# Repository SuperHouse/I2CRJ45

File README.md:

I2C to RJ45 Breakouts for Light Switch Controller
=================================================

Copyright 2019-2021 SuperHouse Automation Pty Ltd  www.superhouse.tv

These I2C to RJ45 breakouts are one component of the SuperHouse home
automation light switch controller project. They allow light switches
to be connected to a controller such as an Arduino, Raspberry Pi,
or ESP8266/ESP32 board.

The RJ45 sockets on the breakout are connected to I/O channels via
I2C addressable I/O buffers. Each RJ45 socket provides connections for
GND, 12V, and 4 signal lines.

Features:

 * RJ45 sockets for connection to light switches over Cat-5
 * I2C interface with interrupt output

More information on the Light Switch Controller project:

  http://www.superhouse.tv/lsc

The LSC also has its own GitHub repo which includes example firmware:

  https://github.com/SuperHouse/LSC

Purchase these breakouts pre-assembled:

  http://www.superhouse.tv/i2crj45

INSTALLATION
------------
The design is saved as an EAGLE project. EAGLE PCB design software is
available from www.cadsoftusa.com free for non-commercial use. To use
this project download it and place the directory containing these files
into the "eagle" directory on your computer. Then open EAGLE and
navigate to the project.

CREDITS
-------
Designed by Jonathan Oxer jon@oxer.com.au

Mechanical drawings by Aaron Knox

DISTRIBUTION
------------
The specific terms of distribution of this project are governed by the
license referenced below.

LICENSE
-------
Licensed under the TAPR Open Hardware License (www.tapr.org/OHL).
The "license" folder within this repository also contains a copy of
this license in plain text format.

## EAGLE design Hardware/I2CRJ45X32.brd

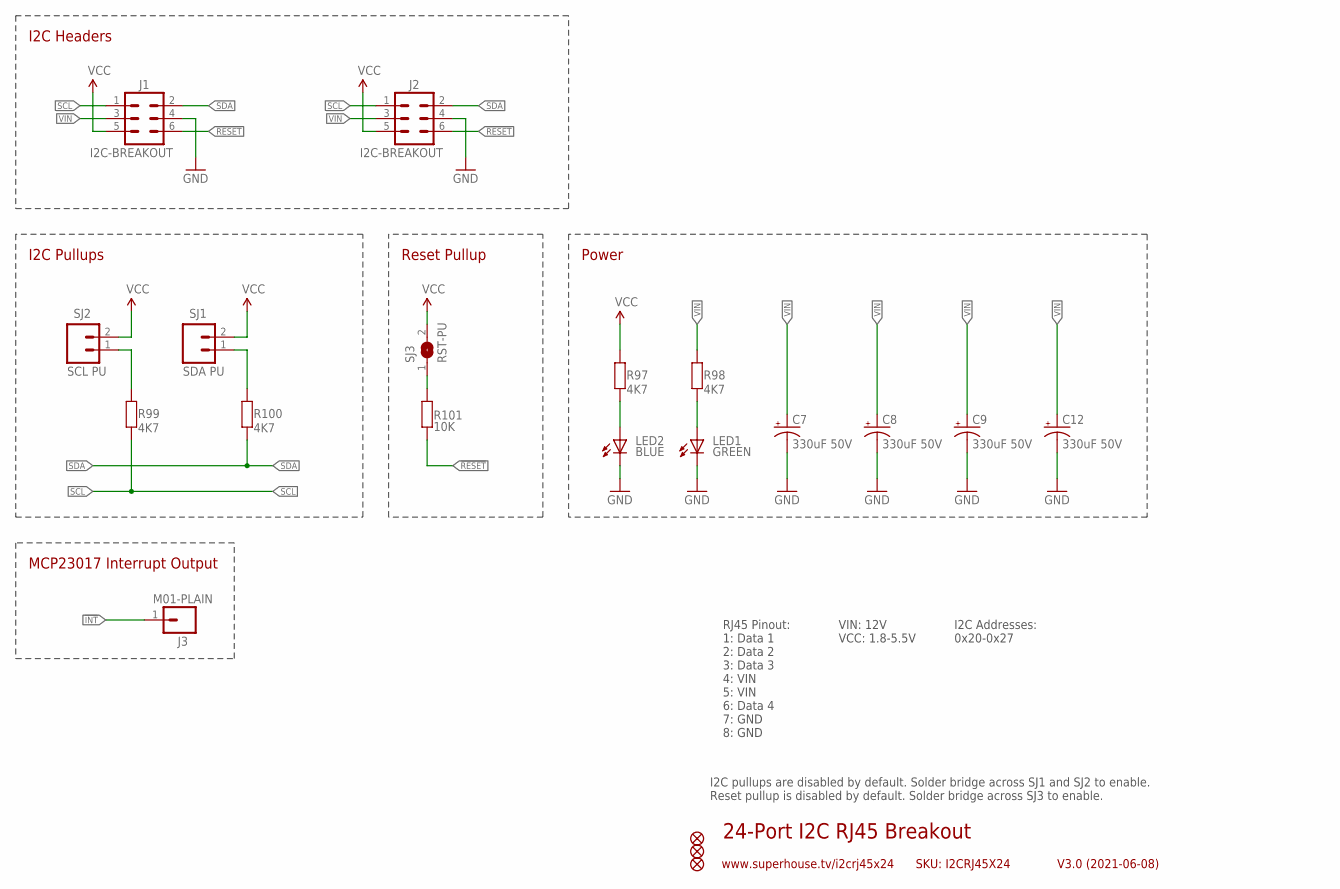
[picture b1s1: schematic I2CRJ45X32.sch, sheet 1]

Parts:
C7, C8, C9, C12: 330uF 50V; PANASONIC_G
FID1, FID2, FID3: FIDUCIAL1X2.5; FIDUCIAL-1X2.5
J1, J2: I2C-BREAKOUT; 2X3-2.54-SHROUDED
J3: M01-PLAIN; 1X01
LED1: GREEN; LED-0603
LED2: BLUE; LED-0603
R97, R98, R99, R100: 4K7; R0603
R101: 10K; R0603
SJ1: SDA PU; 1X02-P
SJ2: SCL PU; 1X02-P
SJ3: RST-PU; SJ

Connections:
!INT: J3.1; also elsewhere on the board
!RESET: J1.6, J2.6, R101.1; also elsewhere on the board
GND: C7.-, C8.-, C9.-, C12.-, J1.4, J2.4, LED1.C, LED2.C; also elsewhere on the board
unnamed: R99.2, SJ2.1
unnamed: R100.2, SJ1.1
unnamed: R101.2, SJ3.1
unnamed: LED2.A, R97.1
unnamed: LED1.A, R98.1
SCL: J1.1, J2.1, R99.1; also elsewhere on the board
SDA: J1.2, J2.2, R100.1; also elsewhere on the board
VCC: J1.5, J2.5, R97.2, SJ1.2, SJ2.2, SJ3.2; also elsewhere on the board
VIN: C7.+, C8.+, C9.+, C12.+, J1.3, J2.3, R98.2; also elsewhere on the board

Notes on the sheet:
24-Port I2C RJ45 Breakout
V3.0 (2021-06-08)
www.superhouse.tv/i2crj45x24
SKU: I2CRJ45X24
RJ45 Pinout: 1: Data 1 2: Data 2 3: Data 3 4: VIN 5: VIN 6: Data 4 7: GND 8: GND
VIN: 12V VCC: 1.8-5.5V
I2C Addresses: 0x20-0x27
I2C Headers
MCP23017 Interrupt Output
I2C Pullups
I2C pullups are disabled by default. Solder bridge across SJ1 and SJ2 to enable. Reset pullup is disabled by default. Solder bridge across SJ3 to enable.
Power
Reset Pullup

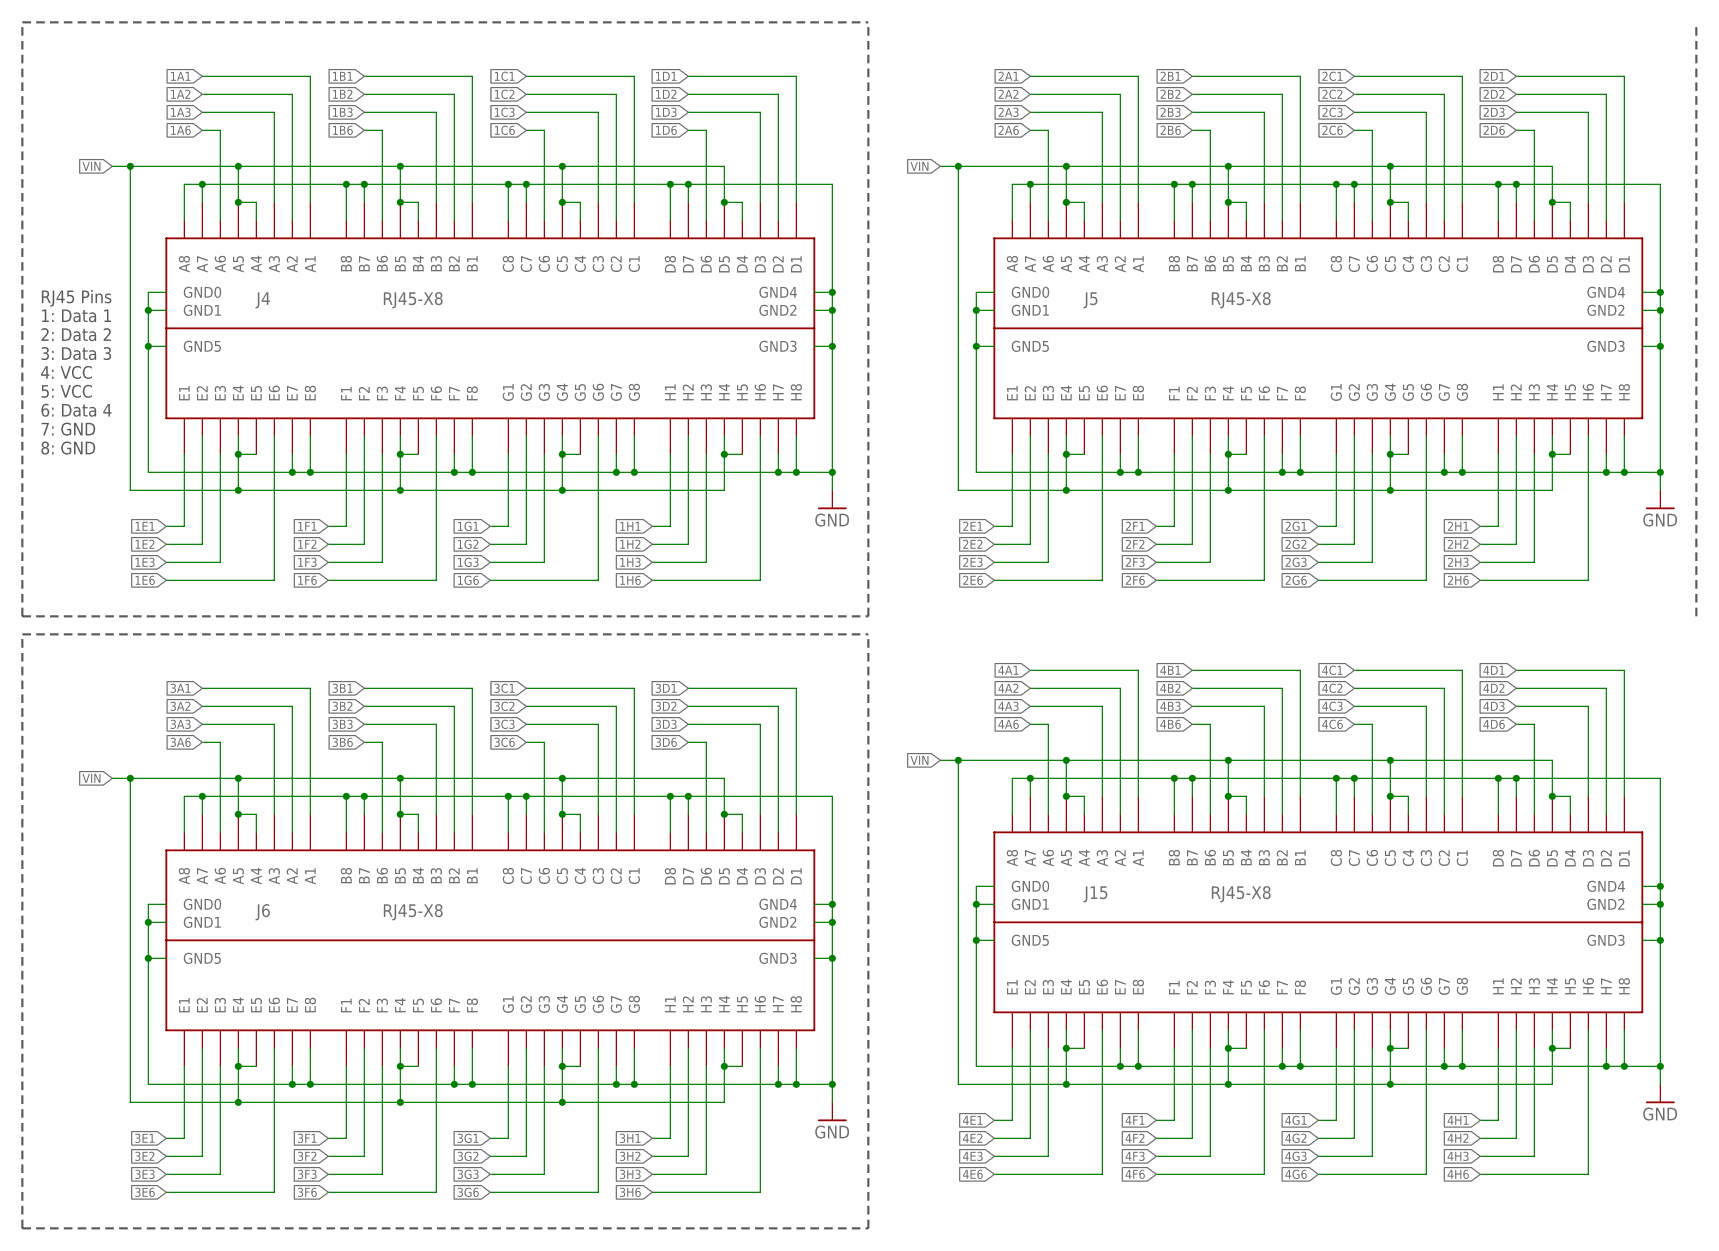
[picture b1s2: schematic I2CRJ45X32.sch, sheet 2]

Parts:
J4, J5, J6, J15: RJ45-X8; RJ45-2X4

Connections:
1A1: J4.A1; also elsewhere on the board
1A2: J4.A2; also elsewhere on the board
1A3: J4.A3; also elsewhere on the board
1A6: J4.A6; also elsewhere on the board
1B1: J4.B1; also elsewhere on the board
1B2: J4.B2; also elsewhere on the board
1B3: J4.B3; also elsewhere on the board
1B6: J4.B6; also elsewhere on the board
1C1: J4.C1; also elsewhere on the board
1C2: J4.C2; also elsewhere on the board
1C3: J4.C3; also elsewhere on the board
1C6: J4.C6; also elsewhere on the board
1D1: J4.D1; also elsewhere on the board
1D2: J4.D2; also elsewhere on the board
1D3: J4.D3; also elsewhere on the board
1D6: J4.D6; also elsewhere on the board
1E1: J4.E1; also elsewhere on the board
1E2: J4.E2; also elsewhere on the board
1E3: J4.E3; also elsewhere on the board
1E6: J4.E6; also elsewhere on the board
1F1: J4.F1; also elsewhere on the board
1F2: J4.F2; also elsewhere on the board
1F3: J4.F3; also elsewhere on the board
1F6: J4.F6; also elsewhere on the board
1G1: J4.G1; also elsewhere on the board
1G2: J4.G2; also elsewhere on the board
1G3: J4.G3; also elsewhere on the board
1G6: J4.G6; also elsewhere on the board
1H1: J4.H1; also elsewhere on the board
1H2: J4.H2; also elsewhere on the board
1H3: J4.H3; also elsewhere on the board
1H6: J4.H6; also elsewhere on the board
2A1: J5.A1; also elsewhere on the board
2A2: J5.A2; also elsewhere on the board
2A3: J5.A3; also elsewhere on the board
2A6: J5.A6; also elsewhere on the board
2B1: J5.B1; also elsewhere on the board
2B2: J5.B2; also elsewhere on the board
2B3: J5.B3; also elsewhere on the board
2B6: J5.B6; also elsewhere on the board
2C1: J5.C1; also elsewhere on the board
2C2: J5.C2; also elsewhere on the board
2C3: J5.C3; also elsewhere on the board
2C6: J5.C6; also elsewhere on the board
2D1: J5.D1; also elsewhere on the board
2D2: J5.D2; also elsewhere on the board
2D3: J5.D3; also elsewhere on the board
2D6: J5.D6; also elsewhere on the board
2E1: J5.E1; also elsewhere on the board
2E2: J5.E2; also elsewhere on the board
2E3: J5.E3; also elsewhere on the board
2E6: J5.E6; also elsewhere on the board
2F1: J5.F1; also elsewhere on the board
2F2: J5.F2; also elsewhere on the board
2F3: J5.F3; also elsewhere on the board
2F6: J5.F6; also elsewhere on the board
2G1: J5.G1; also elsewhere on the board
2G2: J5.G2; also elsewhere on the board
2G3: J5.G3; also elsewhere on the board
2G6: J5.G6; also elsewhere on the board
2H1: J5.H1; also elsewhere on the board
2H2: J5.H2; also elsewhere on the board
2H3: J5.H3; also elsewhere on the board
2H6: J5.H6; also elsewhere on the board
3A1: J6.A1; also elsewhere on the board
3A2: J6.A2; also elsewhere on the board
3A3: J6.A3; also elsewhere on the board
3A6: J6.A6; also elsewhere on the board
3B1: J6.B1; also elsewhere on the board
3B2: J6.B2; also elsewhere on the board
3B3: J6.B3; also elsewhere on the board
3B6: J6.B6; also elsewhere on the board
3C1: J6.C1; also elsewhere on the board
3C2: J6.C2; also elsewhere on the board
3C3: J6.C3; also elsewhere on the board
3C6: J6.C6; also elsewhere on the board
3D1: J6.D1; also elsewhere on the board
3D2: J6.D2; also elsewhere on the board
3D3: J6.D3; also elsewhere on the board
3D6: J6.D6; also elsewhere on the board
3E1: J6.E1; also elsewhere on the board
3E2: J6.E2; also elsewhere on the board
3E3: J6.E3; also elsewhere on the board
3E6: J6.E6; also elsewhere on the board
3F1: J6.F1; also elsewhere on the board
3F2: J6.F2; also elsewhere on the board
3F3: J6.F3; also elsewhere on the board
3F6: J6.F6; also elsewhere on the board
3G1: J6.G1; also elsewhere on the board
3G2: J6.G2; also elsewhere on the board
3G3: J6.G3; also elsewhere on the board
3G6: J6.G6; also elsewhere on the board
3H1: J6.H1; also elsewhere on the board
3H2: J6.H2; also elsewhere on the board
3H3: J6.H3; also elsewhere on the board
3H6: J6.H6; also elsewhere on the board
4A1: J15.A1; also elsewhere on the board
4A2: J15.A2; also elsewhere on the board
4A3: J15.A3; also elsewhere on the board
4A6: J15.A6; also elsewhere on the board
4B1: J15.B1; also elsewhere on the board
4B2: J15.B2; also elsewhere on the board
4B3: J15.B3; also elsewhere on the board
4B6: J15.B6; also elsewhere on the board
4C1: J15.C1; also elsewhere on the board
4C2: J15.C2; also elsewhere on the board
4C3: J15.C3; also elsewhere on the board
4C6: J15.C6; also elsewhere on the board
4D1: J15.D1; also elsewhere on the board
4D2: J15.D2; also elsewhere on the board
4D3: J15.D3; also elsewhere on the board
4D6: J15.D6; also elsewhere on the board
4E1: J15.E1; also elsewhere on the board
4E2: J15.E2; also elsewhere on the board
4E3: J15.E3; also elsewhere on the board
4E6: J15.E6; also elsewhere on the board
4F1: J15.F1; also elsewhere on the board
4F2: J15.F2; also elsewhere on the board
4F3: J15.F3; also elsewhere on the board
4F6: J15.F6; also elsewhere on the board
4G1: J15.G1; also elsewhere on the board
4G2: J15.G2; also elsewhere on the board
4G3: J15.G3; also elsewhere on the board
4G6: J15.G6; also elsewhere on the board
4H1: J15.H1; also elsewhere on the board
4H2: J15.H2; also elsewhere on the board
4H3: J15.H3; also elsewhere on the board
4H6: J15.H6; also elsewhere on the board
GND: J4.A7, J4.A8, J4.B7, J4.B8, J4.C7, J4.C8, J4.D7, J4.D8, J4.E7, J4.E8, J4.F7, J4.F8, J4.G7, J4.G8, J4.GND0, J4.GND1, J4.GND2, J4.GND3, J4.GND4, J4.GND5, J4.H7, J4.H8, J5.A7, J5.A8, J5.B7, J5.B8, J5.C7, J5.C8, J5.D7, J5.D8, J5.E7, J5.E8, J5.F7, J5.F8, J5.G7, J5.G8, J5.GND0, J5.GND1, J5.GND2, J5.GND3, J5.GND4, J5.GND5, J5.H7, J5.H8, J6.A7, J6.A8, J6.B7, J6.B8, J6.C7, J6.C8, J6.D7, J6.D8, J6.E7, J6.E8, J6.F7, J6.F8, J6.G7, J6.G8, J6.GND0, J6.GND1, J6.GND2, J6.GND3, J6.GND4, J6.GND5, J6.H7, J6.H8, J15.A7, J15.A8, J15.B7, J15.B8, J15.C7, J15.C8, J15.D7, J15.D8, J15.E7, J15.E8, J15.F7, J15.F8, J15.G7, J15.G8, J15.GND0, J15.GND1, J15.GND2, J15.GND3, J15.GND4, J15.GND5, J15.H7, J15.H8; also elsewhere on the board
VIN: J4.A4, J4.A5, J4.B4, J4.B5, J4.C4, J4.C5, J4.D4, J4.D5, J4.E4, J4.E5, J4.F4, J4.F5, J4.G4, J4.G5, J4.H4, J4.H5, J5.A4, J5.A5, J5.B4, J5.B5, J5.C4, J5.C5, J5.D4, J5.D5, J5.E4, J5.E5, J5.F4, J5.F5, J5.G4, J5.G5, J5.H4, J5.H5, J6.A4, J6.A5, J6.B4, J6.B5, J6.C4, J6.C5, J6.D4, J6.D5, J6.E4, J6.E5, J6.F4, J6.F5, J6.G4, J6.G5, J6.H4, J6.H5, J15.A4, J15.A5, J15.B4, J15.B5, J15.C4, J15.C5, J15.D4, J15.D5, J15.E4, J15.E5, J15.F4, J15.F5, J15.G4, J15.G5, J15.H4, J15.H5; also elsewhere on the board

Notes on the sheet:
RJ45 Pins 1: Data 1 2: Data 2 3: Data 3 4: VCC 5: VCC 6: Data 4 7: GND 8: GND

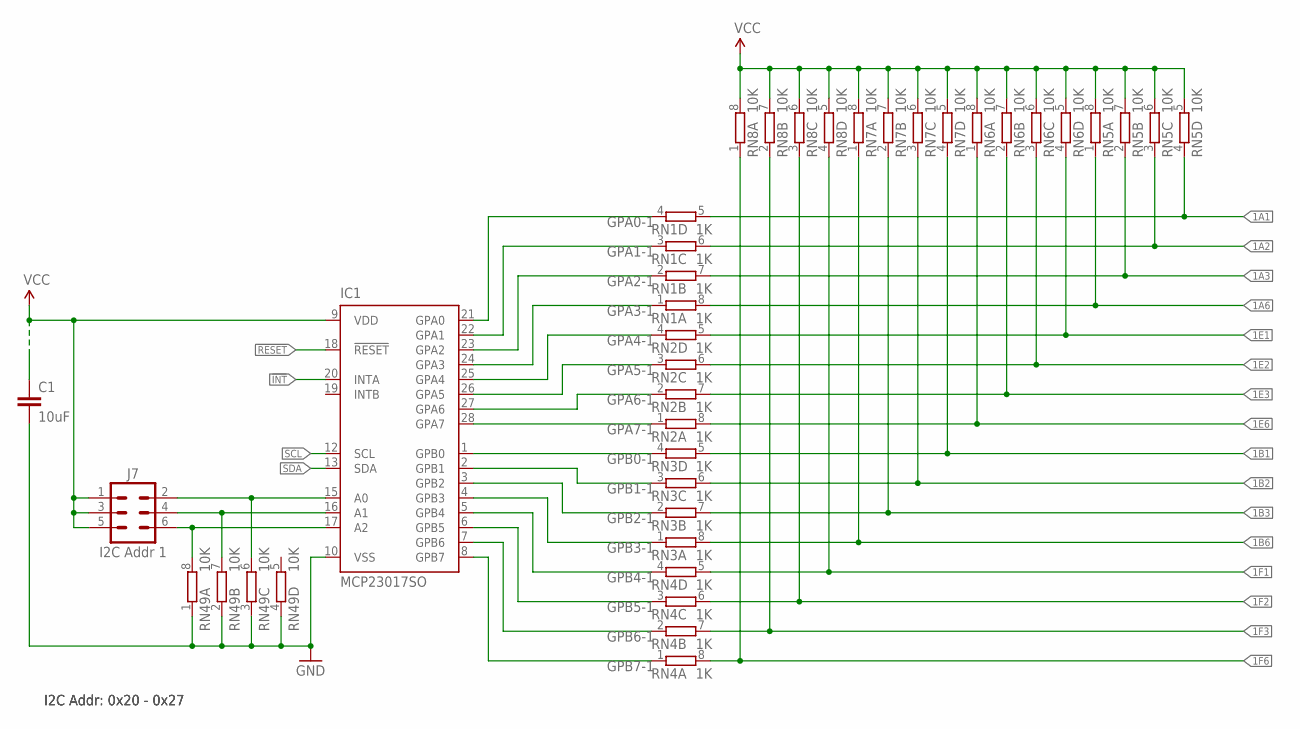
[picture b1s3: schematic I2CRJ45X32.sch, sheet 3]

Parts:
C1: 10uF; C0805
IC1: MCP23017SO; SO28W
J7: I2C Addr 1; 2X03-P
RN1, RN2, RN3, RN4: 1K; CAY16
RN5, RN6, RN7, RN8, RN49: 10K; CAY16

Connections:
1A1: RN1.5 (2), RN5.4 (1); also elsewhere on the board
1A2: RN1.6 (2), RN5.3 (1); also elsewhere on the board
1A3: RN1.7 (2), RN5.2 (1); also elsewhere on the board
1A6: RN1.8 (2), RN5.1; also elsewhere on the board
1B1: RN3.5 (2), RN7.4 (1); also elsewhere on the board
1B2: RN3.6 (2), RN7.3 (1); also elsewhere on the board
1B3: RN3.7 (2), RN7.2 (1); also elsewhere on the board
1B6: RN3.8 (2), RN7.1; also elsewhere on the board
1E1: RN2.5 (2), RN6.4 (1); also elsewhere on the board
1E2: RN2.6 (2), RN6.3 (1); also elsewhere on the board
1E3: RN2.7 (2), RN6.2 (1); also elsewhere on the board
1E6: RN2.8 (2), RN6.1; also elsewhere on the board
1F1: RN4.5 (2), RN8.4 (1); also elsewhere on the board
1F2: RN4.6 (2), RN8.3 (1); also elsewhere on the board
1F3: RN4.7 (2), RN8.2 (1); also elsewhere on the board
1F6: RN4.8 (2), RN8.1; also elsewhere on the board
!INT: IC1.20 (INTA); also elsewhere on the board
!RESET: IC1.18 (!RESET); also elsewhere on the board
GND: C1.2, IC1.10 (VSS), RN49.1, RN49.2 (1), RN49.3 (1), RN49.4 (1); also elsewhere on the board
GPA0-1: IC1.21 (GPA0), RN1.4 (1)
GPA1-1: IC1.22 (GPA1), RN1.3 (1)
GPA2-1: IC1.23 (GPA2), RN1.2 (1)
GPA3-1: IC1.24 (GPA3), RN1.1
GPA4-1: IC1.25 (GPA4), RN2.4 (1)
GPA5-1: IC1.26 (GPA5), RN2.3 (1)
GPA6-1: IC1.27 (GPA6), RN2.2 (1)
GPA7-1: IC1.28 (GPA7), RN2.1
GPB0-1: IC1.1 (GPB0), RN3.4 (1)
GPB1-1: IC1.2 (GPB1), RN3.3 (1)
GPB2-1: IC1.3 (GPB2), RN3.2 (1)
GPB3-1: IC1.4 (GPB3), RN3.1
GPB4-1: IC1.5 (GPB4), RN4.4 (1)
GPB5-1: IC1.6 (GPB5), RN4.3 (1)
GPB6-1: IC1.7 (GPB6), RN4.2 (1)
GPB7-1: IC1.8 (GPB7), RN4.1
unnamed: IC1.17 (A2), J7.6, RN49.8 (2)
unnamed: IC1.16 (A1), J7.4, RN49.7 (2)
unnamed: IC1.15 (A0), J7.2, RN49.6 (2)
SCL: IC1.12 (SCL); also elsewhere on the board
SDA: IC1.13 (SDA); also elsewhere on the board
VCC: C1.1, IC1.9 (VDD), J7.1, J7.3, J7.5, RN5.5 (2), RN5.6 (2), RN5.7 (2), RN5.8 (2), RN6.5 (2), RN6.6 (2), RN6.7 (2), RN6.8 (2), RN7.5 (2), RN7.6 (2), RN7.7 (2), RN7.8 (2), RN8.5 (2), RN8.6 (2), RN8.7 (2), RN8.8 (2); also elsewhere on the board

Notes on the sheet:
I2C Addr: 0x20 - 0x27

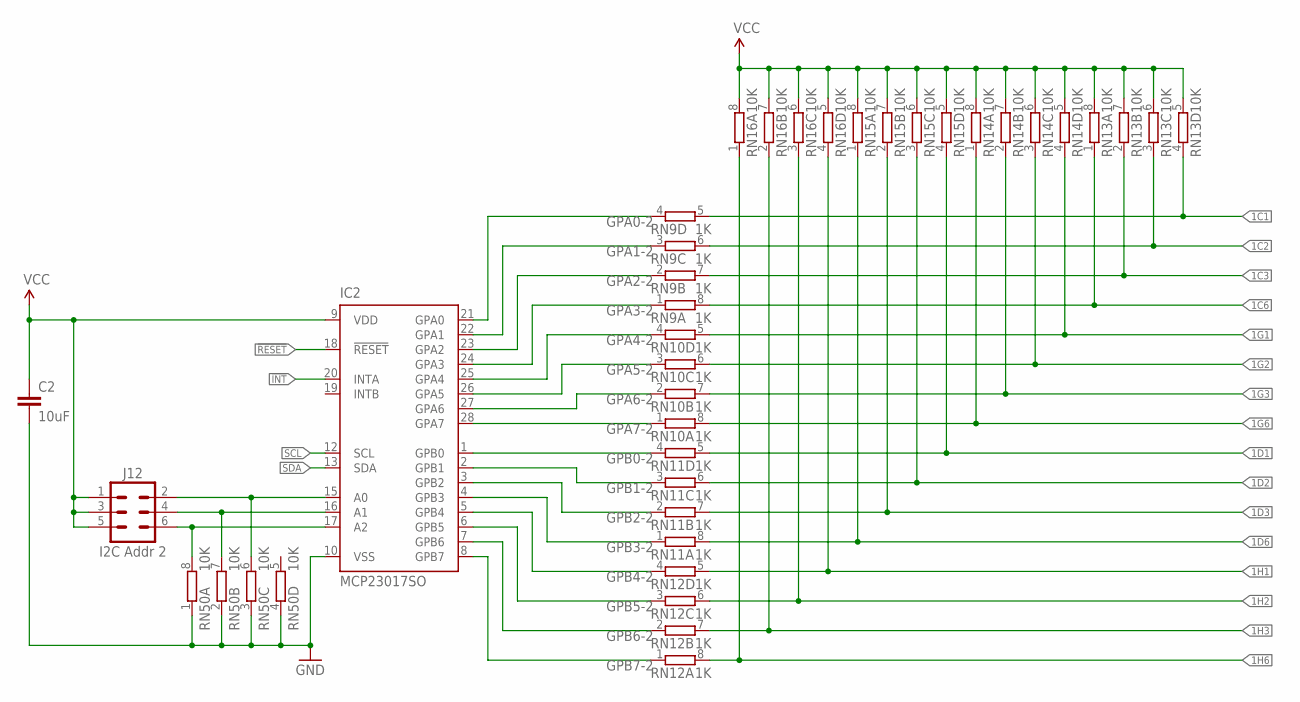
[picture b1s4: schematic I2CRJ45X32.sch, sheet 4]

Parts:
C2: 10uF; C0805
IC2: MCP23017SO; SO28W
J12: I2C Addr 2; 2X03-P
RN9, RN10, RN11, RN12: 1K; CAY16
RN13, RN14, RN15, RN16, RN50: 10K; CAY16

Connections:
1C1: RN9.5 (2), RN13.4 (1); also elsewhere on the board
1C2: RN9.6 (2), RN13.3 (1); also elsewhere on the board
1C3: RN9.7 (2), RN13.2 (1); also elsewhere on the board
1C6: RN9.8 (2), RN13.1; also elsewhere on the board
1D1: RN11.5 (2), RN15.4 (1); also elsewhere on the board
1D2: RN11.6 (2), RN15.3 (1); also elsewhere on the board
1D3: RN11.7 (2), RN15.2 (1); also elsewhere on the board
1D6: RN11.8 (2), RN15.1; also elsewhere on the board
1G1: RN10.5 (2), RN14.4 (1); also elsewhere on the board
1G2: RN10.6 (2), RN14.3 (1); also elsewhere on the board
1G3: RN10.7 (2), RN14.2 (1); also elsewhere on the board
1G6: RN10.8 (2), RN14.1; also elsewhere on the board
1H1: RN12.5 (2), RN16.4 (1); also elsewhere on the board
1H2: RN12.6 (2), RN16.3 (1); also elsewhere on the board
1H3: RN12.7 (2), RN16.2 (1); also elsewhere on the board
1H6: RN12.8 (2), RN16.1; also elsewhere on the board
!INT: IC2.20 (INTA); also elsewhere on the board
!RESET: IC2.18 (!RESET); also elsewhere on the board
GND: C2.2, IC2.10 (VSS), RN50.1, RN50.2 (1), RN50.3 (1), RN50.4 (1); also elsewhere on the board
GPA0-2: IC2.21 (GPA0), RN9.4 (1)
GPA1-2: IC2.22 (GPA1), RN9.3 (1)
GPA2-2: IC2.23 (GPA2), RN9.2 (1)
GPA3-2: IC2.24 (GPA3), RN9.1
GPA4-2: IC2.25 (GPA4), RN10.4 (1)
GPA5-2: IC2.26 (GPA5), RN10.3 (1)
GPA6-2: IC2.27 (GPA6), RN10.2 (1)
GPA7-2: IC2.28 (GPA7), RN10.1
GPB0-2: IC2.1 (GPB0), RN11.4 (1)
GPB1-2: IC2.2 (GPB1), RN11.3 (1)
GPB2-2: IC2.3 (GPB2), RN11.2 (1)
GPB3-2: IC2.4 (GPB3), RN11.1
GPB4-2: IC2.5 (GPB4), RN12.4 (1)
GPB5-2: IC2.6 (GPB5), RN12.3 (1)
GPB6-2: IC2.7 (GPB6), RN12.2 (1)
GPB7-2: IC2.8 (GPB7), RN12.1
unnamed: IC2.15 (A0), J12.2, RN50.6 (2)
unnamed: IC2.16 (A1), J12.4, RN50.7 (2)
unnamed: IC2.17 (A2), J12.6, RN50.8 (2)
SCL: IC2.12 (SCL); also elsewhere on the board
SDA: IC2.13 (SDA); also elsewhere on the board
VCC: C2.1, IC2.9 (VDD), J12.1, J12.3, J12.5, RN13.5 (2), RN13.6 (2), RN13.7 (2), RN13.8 (2), RN14.5 (2), RN14.6 (2), RN14.7 (2), RN14.8 (2), RN15.5 (2), RN15.6 (2), RN15.7 (2), RN15.8 (2), RN16.5 (2), RN16.6 (2), RN16.7 (2), RN16.8 (2); also elsewhere on the board

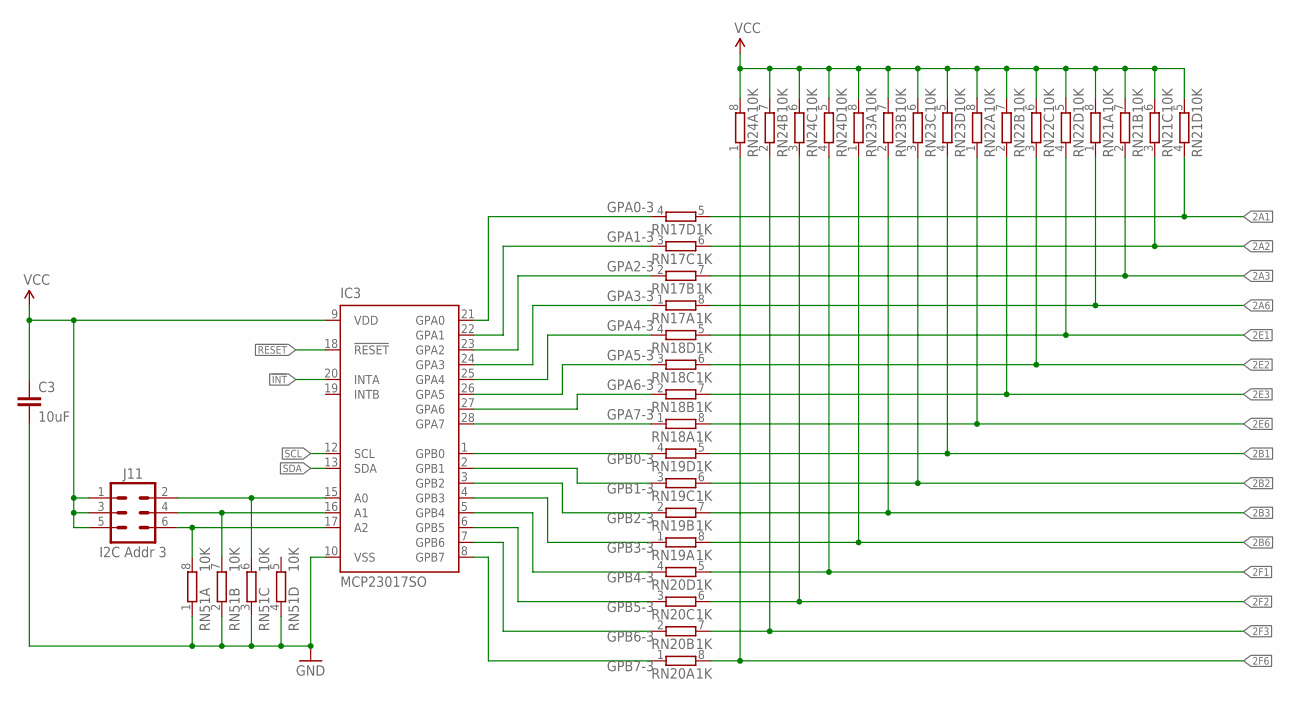
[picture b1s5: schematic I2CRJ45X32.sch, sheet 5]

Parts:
C3: 10uF; C0805
IC3: MCP23017SO; SO28W
J11: I2C Addr 3; 2X03-P
RN17, RN18, RN19, RN20: 1K; CAY16
RN21, RN22, RN23, RN24, RN51: 10K; CAY16

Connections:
2A1: RN17.5 (2), RN21.4 (1); also elsewhere on the board
2A2: RN17.6 (2), RN21.3 (1); also elsewhere on the board
2A3: RN17.7 (2), RN21.2 (1); also elsewhere on the board
2A6: RN17.8 (2), RN21.1; also elsewhere on the board
2B1: RN19.5 (2), RN23.4 (1); also elsewhere on the board
2B2: RN19.6 (2), RN23.3 (1); also elsewhere on the board
2B3: RN19.7 (2), RN23.2 (1); also elsewhere on the board
2B6: RN19.8 (2), RN23.1; also elsewhere on the board
2E1: RN18.5 (2), RN22.4 (1); also elsewhere on the board
2E2: RN18.6 (2), RN22.3 (1); also elsewhere on the board
2E3: RN18.7 (2), RN22.2 (1); also elsewhere on the board
2E6: RN18.8 (2), RN22.1; also elsewhere on the board
2F1: RN20.5 (2), RN24.4 (1); also elsewhere on the board
2F2: RN20.6 (2), RN24.3 (1); also elsewhere on the board
2F3: RN20.7 (2), RN24.2 (1); also elsewhere on the board
2F6: RN20.8 (2), RN24.1; also elsewhere on the board
!INT: IC3.20 (INTA); also elsewhere on the board
!RESET: IC3.18 (!RESET); also elsewhere on the board
GND: C3.2, IC3.10 (VSS), RN51.1, RN51.2 (1), RN51.3 (1), RN51.4 (1); also elsewhere on the board
GPA0-3: IC3.21 (GPA0), RN17.4 (1)
GPA1-3: IC3.22 (GPA1), RN17.3 (1)
GPA2-3: IC3.23 (GPA2), RN17.2 (1)
GPA3-3: IC3.24 (GPA3), RN17.1
GPA4-3: IC3.25 (GPA4), RN18.4 (1)
GPA5-3: IC3.26 (GPA5), RN18.3 (1)
GPA6-3: IC3.27 (GPA6), RN18.2 (1)
GPA7-3: IC3.28 (GPA7), RN18.1
GPB0-3: IC3.1 (GPB0), RN19.4 (1)
GPB1-3: IC3.2 (GPB1), RN19.3 (1)
GPB2-3: IC3.3 (GPB2), RN19.2 (1)
GPB3-3: IC3.4 (GPB3), RN19.1
GPB4-3: IC3.5 (GPB4), RN20.4 (1)
GPB5-3: IC3.6 (GPB5), RN20.3 (1)
GPB6-3: IC3.7 (GPB6), RN20.2 (1)
GPB7-3: IC3.8 (GPB7), RN20.1
unnamed: IC3.17 (A2), J11.6, RN51.8 (2)
unnamed: IC3.15 (A0), J11.2, RN51.6 (2)
unnamed: IC3.16 (A1), J11.4, RN51.7 (2)
SCL: IC3.12 (SCL); also elsewhere on the board
SDA: IC3.13 (SDA); also elsewhere on the board
VCC: C3.1, IC3.9 (VDD), J11.1, J11.3, J11.5, RN21.5 (2), RN21.6 (2), RN21.7 (2), RN21.8 (2), RN22.5 (2), RN22.6 (2), RN22.7 (2), RN22.8 (2), RN23.5 (2), RN23.6 (2), RN23.7 (2), RN23.8 (2), RN24.5 (2), RN24.6 (2), RN24.7 (2), RN24.8 (2); also elsewhere on the board

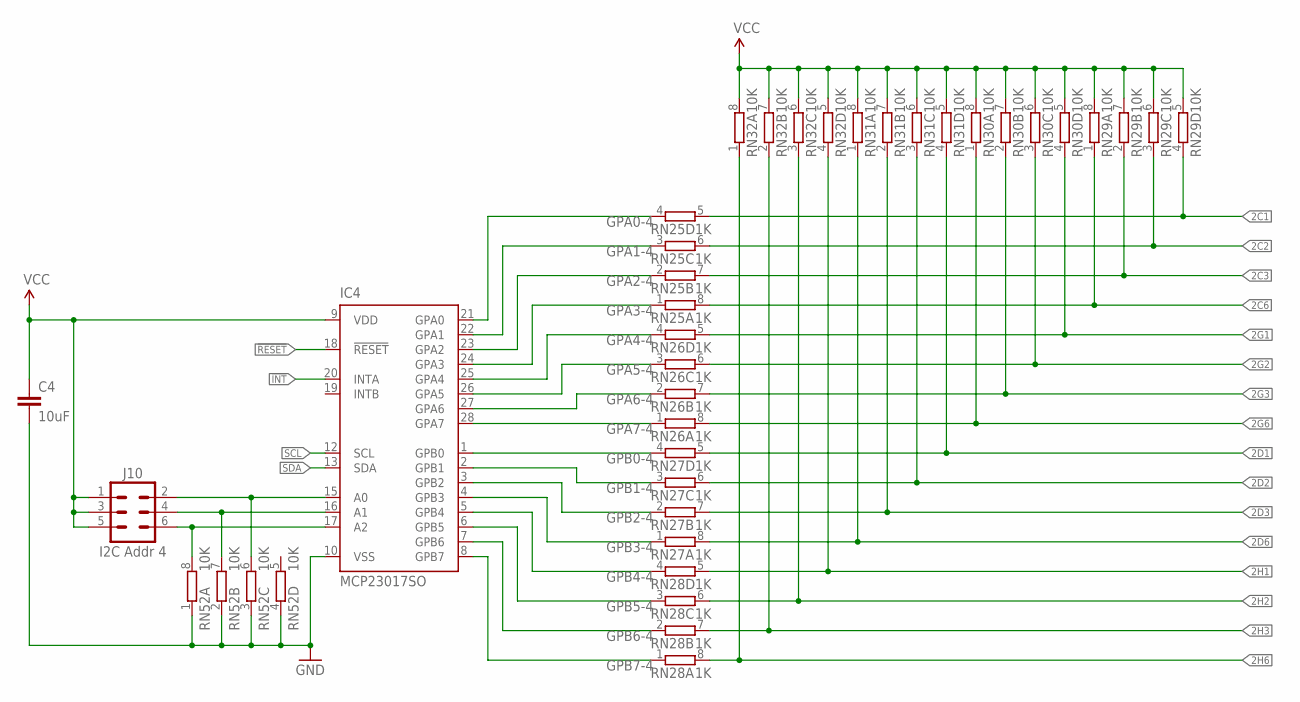
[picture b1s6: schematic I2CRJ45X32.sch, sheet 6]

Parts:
C4: 10uF; C0805
IC4: MCP23017SO; SO28W
J10: I2C Addr 4; 2X03-P
RN25, RN26, RN27, RN28: 1K; CAY16
RN29, RN30, RN31, RN32, RN52: 10K; CAY16

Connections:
2C1: RN25.5 (2), RN29.4 (1); also elsewhere on the board
2C2: RN25.6 (2), RN29.3 (1); also elsewhere on the board
2C3: RN25.7 (2), RN29.2 (1); also elsewhere on the board
2C6: RN25.8 (2), RN29.1; also elsewhere on the board
2D1: RN27.5 (2), RN31.4 (1); also elsewhere on the board
2D2: RN27.6 (2), RN31.3 (1); also elsewhere on the board
2D3: RN27.7 (2), RN31.2 (1); also elsewhere on the board
2D6: RN27.8 (2), RN31.1; also elsewhere on the board
2G1: RN26.5 (2), RN30.4 (1); also elsewhere on the board
2G2: RN26.6 (2), RN30.3 (1); also elsewhere on the board
2G3: RN26.7 (2), RN30.2 (1); also elsewhere on the board
2G6: RN26.8 (2), RN30.1; also elsewhere on the board
2H1: RN28.5 (2), RN32.4 (1); also elsewhere on the board
2H2: RN28.6 (2), RN32.3 (1); also elsewhere on the board
2H3: RN28.7 (2), RN32.2 (1); also elsewhere on the board
2H6: RN28.8 (2), RN32.1; also elsewhere on the board
!INT: IC4.20 (INTA); also elsewhere on the board
!RESET: IC4.18 (!RESET); also elsewhere on the board
GND: C4.2, IC4.10 (VSS), RN52.1, RN52.2 (1), RN52.3 (1), RN52.4 (1); also elsewhere on the board
GPA0-4: IC4.21 (GPA0), RN25.4 (1)
GPA1-4: IC4.22 (GPA1), RN25.3 (1)
GPA2-4: IC4.23 (GPA2), RN25.2 (1)
GPA3-4: IC4.24 (GPA3), RN25.1
GPA4-4: IC4.25 (GPA4), RN26.4 (1)
GPA5-4: IC4.26 (GPA5), RN26.3 (1)
GPA6-4: IC4.27 (GPA6), RN26.2 (1)
GPA7-4: IC4.28 (GPA7), RN26.1
GPB0-4: IC4.1 (GPB0), RN27.4 (1)
GPB1-4: IC4.2 (GPB1), RN27.3 (1)
GPB2-4: IC4.3 (GPB2), RN27.2 (1)
GPB3-4: IC4.4 (GPB3), RN27.1
GPB4-4: IC4.5 (GPB4), RN28.4 (1)
GPB5-4: IC4.6 (GPB5), RN28.3 (1)
GPB6-4: IC4.7 (GPB6), RN28.2 (1)
GPB7-4: IC4.8 (GPB7), RN28.1
unnamed: IC4.17 (A2), J10.6, RN52.8 (2)
unnamed: IC4.15 (A0), J10.2, RN52.6 (2)
unnamed: IC4.16 (A1), J10.4, RN52.7 (2)
SCL: IC4.12 (SCL); also elsewhere on the board
SDA: IC4.13 (SDA); also elsewhere on the board
VCC: C4.1, IC4.9 (VDD), J10.1, J10.3, J10.5, RN29.5 (2), RN29.6 (2), RN29.7 (2), RN29.8 (2), RN30.5 (2), RN30.6 (2), RN30.7 (2), RN30.8 (2), RN31.5 (2), RN31.6 (2), RN31.7 (2), RN31.8 (2), RN32.5 (2), RN32.6 (2), RN32.7 (2), RN32.8 (2); also elsewhere on the board

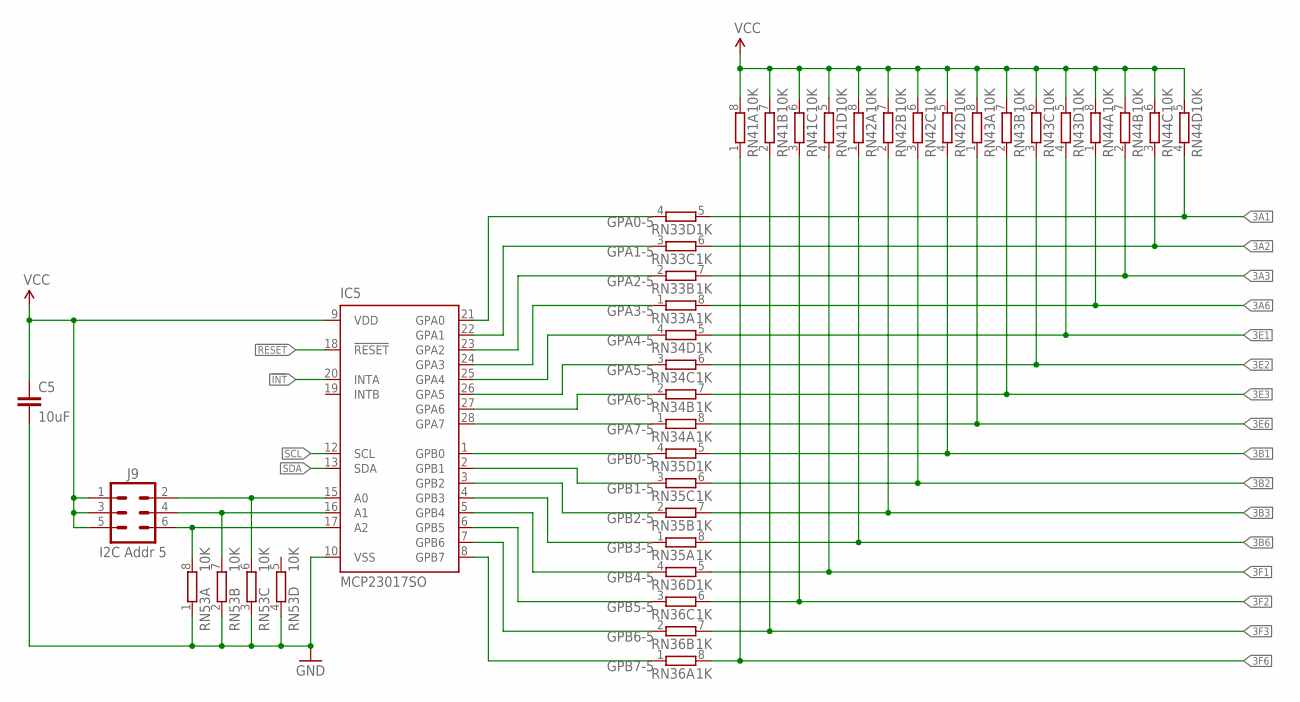
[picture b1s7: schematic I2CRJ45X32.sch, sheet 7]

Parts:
C5: 10uF; C0805
IC5: MCP23017SO; SO28W
J9: I2C Addr 5; 2X03-P
RN33, RN34, RN35, RN36: 1K; CAY16
RN41, RN42, RN43, RN44, RN53: 10K; CAY16

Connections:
3A1: RN33.5 (2), RN44.4 (1); also elsewhere on the board
3A2: RN33.6 (2), RN44.3 (1); also elsewhere on the board
3A3: RN33.7 (2), RN44.2 (1); also elsewhere on the board
3A6: RN33.8 (2), RN44.1; also elsewhere on the board
3B1: RN35.5 (2), RN42.4 (1); also elsewhere on the board
3B2: RN35.6 (2), RN42.3 (1); also elsewhere on the board
3B3: RN35.7 (2), RN42.2 (1); also elsewhere on the board
3B6: RN35.8 (2), RN42.1; also elsewhere on the board
3E1: RN34.5 (2), RN43.4 (1); also elsewhere on the board
3E2: RN34.6 (2), RN43.3 (1); also elsewhere on the board
3E3: RN34.7 (2), RN43.2 (1); also elsewhere on the board
3E6: RN34.8 (2), RN43.1; also elsewhere on the board
3F1: RN36.5 (2), RN41.4 (1); also elsewhere on the board
3F2: RN36.6 (2), RN41.3 (1); also elsewhere on the board
3F3: RN36.7 (2), RN41.2 (1); also elsewhere on the board
3F6: RN36.8 (2), RN41.1; also elsewhere on the board
!INT: IC5.20 (INTA); also elsewhere on the board
!RESET: IC5.18 (!RESET); also elsewhere on the board
GND: C5.2, IC5.10 (VSS), RN53.1, RN53.2 (1), RN53.3 (1), RN53.4 (1); also elsewhere on the board
GPA0-5: IC5.21 (GPA0), RN33.4 (1)
GPA1-5: IC5.22 (GPA1), RN33.3 (1)
GPA2-5: IC5.23 (GPA2), RN33.2 (1)
GPA3-5: IC5.24 (GPA3), RN33.1
GPA4-5: IC5.25 (GPA4), RN34.4 (1)
GPA5-5: IC5.26 (GPA5), RN34.3 (1)
GPA6-5: IC5.27 (GPA6), RN34.2 (1)
GPA7-5: IC5.28 (GPA7), RN34.1
GPB0-5: IC5.1 (GPB0), RN35.4 (1)
GPB1-5: IC5.2 (GPB1), RN35.3 (1)
GPB2-5: IC5.3 (GPB2), RN35.2 (1)
GPB3-5: IC5.4 (GPB3), RN35.1
GPB4-5: IC5.5 (GPB4), RN36.4 (1)
GPB5-5: IC5.6 (GPB5), RN36.3 (1)
GPB6-5: IC5.7 (GPB6), RN36.2 (1)
GPB7-5: IC5.8 (GPB7), RN36.1
unnamed: IC5.17 (A2), J9.6, RN53.8 (2)
unnamed: IC5.15 (A0), J9.2, RN53.6 (2)
unnamed: IC5.16 (A1), J9.4, RN53.7 (2)
SCL: IC5.12 (SCL); also elsewhere on the board
SDA: IC5.13 (SDA); also elsewhere on the board
VCC: C5.1, IC5.9 (VDD), J9.1, J9.3, J9.5, RN41.5 (2), RN41.6 (2), RN41.7 (2), RN41.8 (2), RN42.5 (2), RN42.6 (2), RN42.7 (2), RN42.8 (2), RN43.5 (2), RN43.6 (2), RN43.7 (2), RN43.8 (2), RN44.5 (2), RN44.6 (2), RN44.7 (2), RN44.8 (2); also elsewhere on the board

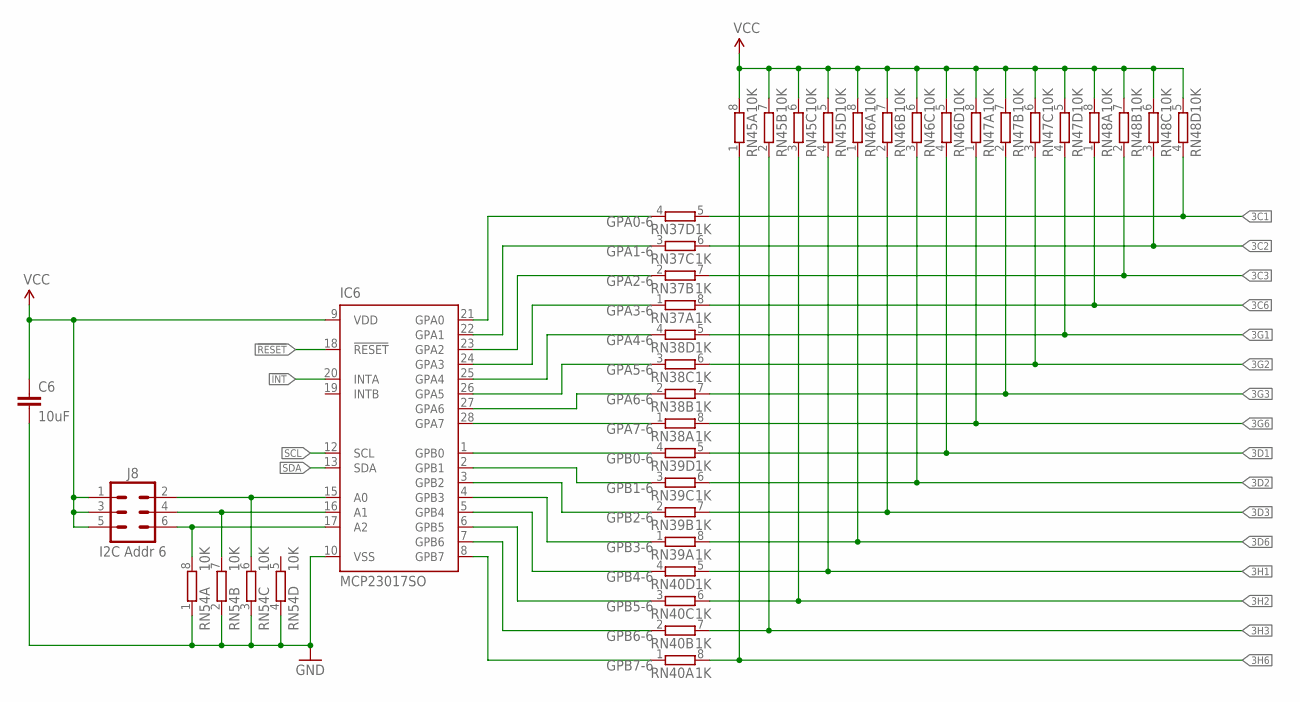
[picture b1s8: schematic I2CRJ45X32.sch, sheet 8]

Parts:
C6: 10uF; C0805
IC6: MCP23017SO; SO28W
J8: I2C Addr 6; 2X03-P
RN37, RN38, RN39, RN40: 1K; CAY16
RN45, RN46, RN47, RN48, RN54: 10K; CAY16

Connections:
3C1: RN37.5 (2), RN48.4 (1); also elsewhere on the board
3C2: RN37.6 (2), RN48.3 (1); also elsewhere on the board
3C3: RN37.7 (2), RN48.2 (1); also elsewhere on the board
3C6: RN37.8 (2), RN48.1; also elsewhere on the board
3D1: RN39.5 (2), RN46.4 (1); also elsewhere on the board
3D2: RN39.6 (2), RN46.3 (1); also elsewhere on the board
3D3: RN39.7 (2), RN46.2 (1); also elsewhere on the board
3D6: RN39.8 (2), RN46.1; also elsewhere on the board
3G1: RN38.5 (2), RN47.4 (1); also elsewhere on the board
3G2: RN38.6 (2), RN47.3 (1); also elsewhere on the board
3G3: RN38.7 (2), RN47.2 (1); also elsewhere on the board
3G6: RN38.8 (2), RN47.1; also elsewhere on the board
3H1: RN40.5 (2), RN45.4 (1); also elsewhere on the board
3H2: RN40.6 (2), RN45.3 (1); also elsewhere on the board
3H3: RN40.7 (2), RN45.2 (1); also elsewhere on the board
3H6: RN40.8 (2), RN45.1; also elsewhere on the board
!INT: IC6.20 (INTA); also elsewhere on the board
!RESET: IC6.18 (!RESET); also elsewhere on the board
GND: C6.2, IC6.10 (VSS), RN54.1, RN54.2 (1), RN54.3 (1), RN54.4 (1); also elsewhere on the board
GPA0-6: IC6.21 (GPA0), RN37.4 (1)
GPA1-6: IC6.22 (GPA1), RN37.3 (1)
GPA2-6: IC6.23 (GPA2), RN37.2 (1)
GPA3-6: IC6.24 (GPA3), RN37.1
GPA4-6: IC6.25 (GPA4), RN38.4 (1)
GPA5-6: IC6.26 (GPA5), RN38.3 (1)
GPA6-6: IC6.27 (GPA6), RN38.2 (1)
GPA7-6: IC6.28 (GPA7), RN38.1
GPB0-6: IC6.1 (GPB0), RN39.4 (1)
GPB1-6: IC6.2 (GPB1), RN39.3 (1)
GPB2-6: IC6.3 (GPB2), RN39.2 (1)
GPB3-6: IC6.4 (GPB3), RN39.1
GPB4-6: IC6.5 (GPB4), RN40.4 (1)
GPB5-6: IC6.6 (GPB5), RN40.3 (1)
GPB6-6: IC6.7 (GPB6), RN40.2 (1)
GPB7-6: IC6.8 (GPB7), RN40.1
unnamed: IC6.17 (A2), J8.6, RN54.8 (2)
unnamed: IC6.15 (A0), J8.2, RN54.6 (2)
unnamed: IC6.16 (A1), J8.4, RN54.7 (2)
SCL: IC6.12 (SCL); also elsewhere on the board
SDA: IC6.13 (SDA); also elsewhere on the board
VCC: C6.1, IC6.9 (VDD), J8.1, J8.3, J8.5, RN45.5 (2), RN45.6 (2), RN45.7 (2), RN45.8 (2), RN46.5 (2), RN46.6 (2), RN46.7 (2), RN46.8 (2), RN47.5 (2), RN47.6 (2), RN47.7 (2), RN47.8 (2), RN48.5 (2), RN48.6 (2), RN48.7 (2), RN48.8 (2); also elsewhere on the board
